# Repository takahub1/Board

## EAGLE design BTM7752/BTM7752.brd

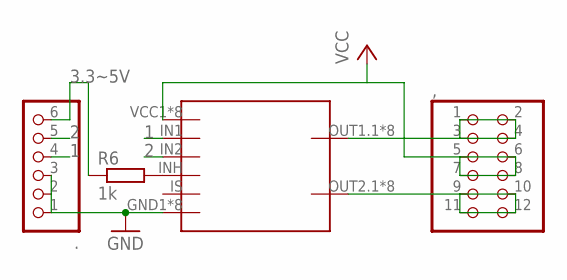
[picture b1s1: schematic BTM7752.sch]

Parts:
,: PINHD-2X6; 2X06
.: PINHD-1X6; 1X06
R6: 1k; R0603
U$1: BTM7752

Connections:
1: ..4, U$1.IN1
2: ..5, U$1.IN2
3.3~5V: ..6, R6.1
GND: ..1, ..2, ..3, U$1.GND1 (GND), U$1.GND2 (GND), U$1.GND3 (GND), U$1.GND4 (GND), U$1.GND5 (GND), U$1.GND6 (GND), U$1.GND7 (GND), U$1.GND8 (GND)
unnamed: ,.9, ,.10, ,.11, ,.12, U$1.OUT2.1 (OUT2), U$1.OUT2.2 (OUT2), U$1.OUT2.3 (OUT2), U$1.OUT2.4 (OUT2), U$1.OUT2.5 (OUT2), U$1.OUT2.6 (OUT2), U$1.OUT2.7 (OUT2), U$1.OUT2.8 (OUT2)
unnamed: ,.1, ,.2, ,.3, ,.4, U$1.OUT1.1 (OUT1), U$1.OUT1.2 (OUT1), U$1.OUT1.3 (OUT1), U$1.OUT1.4 (OUT1), U$1.OUT1.5 (OUT1), U$1.OUT1.6 (OUT1), U$1.OUT1.7 (OUT1), U$1.OUT1.8 (OUT1)
unnamed: R6.2, U$1.INH
VCC: ,.5, ,.6, ,.7, ,.8, U$1.VCC1 (VCC), U$1.VCC2 (VCC), U$1.VCC3 (VCC), U$1.VCC4 (VCC), U$1.VCC5 (VCC), U$1.VCC6 (VCC), U$1.VCC7 (VCC), U$1.VCC8 (VCC)

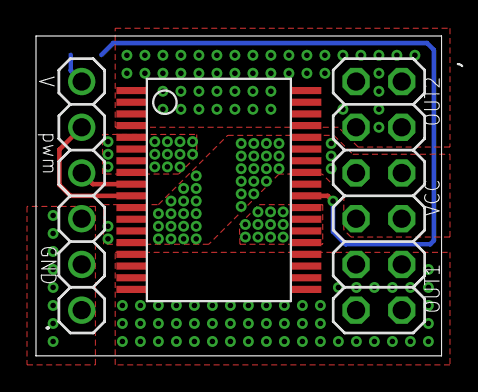
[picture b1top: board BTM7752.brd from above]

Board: 2 copper layers, 22.5 x 17.8 mm, 4 parts (1 on the bottom side), 8 nets.

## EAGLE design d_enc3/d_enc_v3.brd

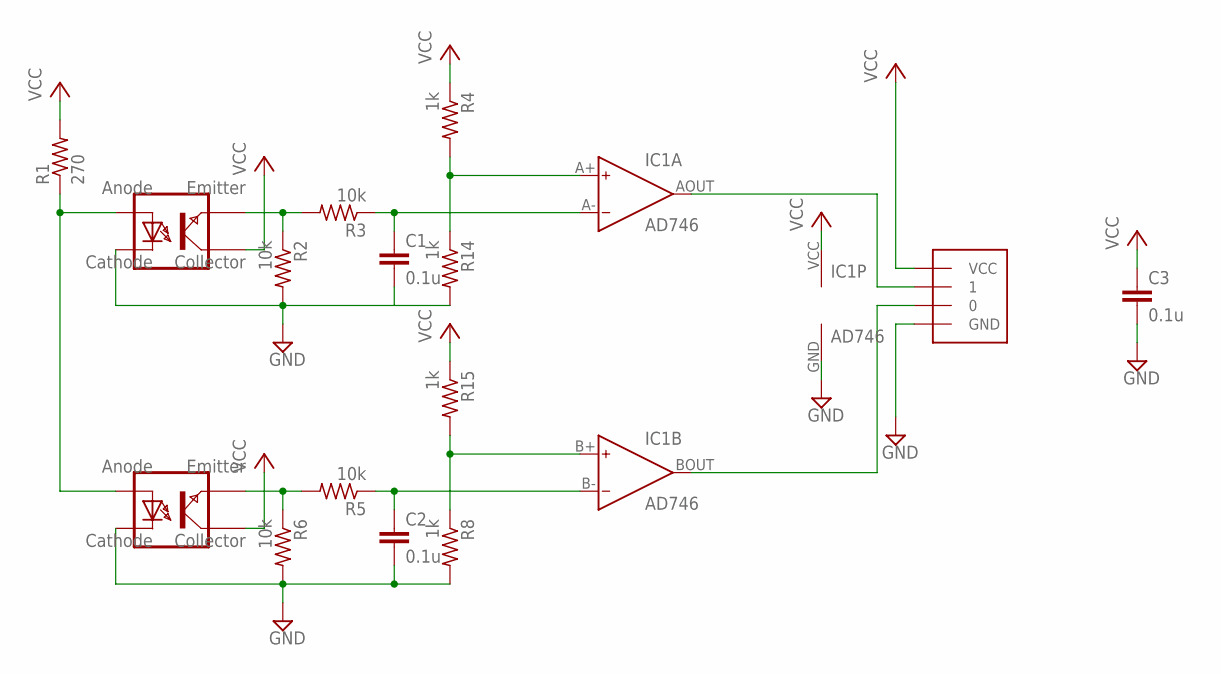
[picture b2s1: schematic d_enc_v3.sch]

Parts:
C1, C2, C3: 0.1u; C0603
IC1: AD746; NJM2903E
R1: 270; R0603
R2, R3, R5, R6: 10k; R0603
R4, R8, R14, R15: 1k; R0603
U$1, U$4: TPR-105F
U$2: ENC_CON

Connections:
GND: C1.2, C2.2, C3.2, IC1.GND (V-), R2.2, R6.2, R8.2, R14.2, U$1.CATHODE, U$2.GND, U$4.CATHODE
unnamed: C1.1, IC1.A- (IN-), R3.1
unnamed: R1.1, U$1.ANODE, U$4.ANODE
unnamed: R2.1, R3.2, U$4.EMITTER
unnamed: R5.2, R6.1, U$1.EMITTER
unnamed: C2.1, IC1.B- (IN-), R5.1
unnamed: IC1.AOUT (OUT), U$2.1
unnamed: IC1.BOUT (OUT), U$2.0
unnamed: IC1.B+ (IN+), R8.1, R15.2
unnamed: IC1.A+ (IN+), R4.2, R14.1
VCC: C3.1, IC1.VCC (V+), R1.2, R4.1, R15.1, U$1.COLLECTOR, U$2.VCC, U$4.COLLECTOR

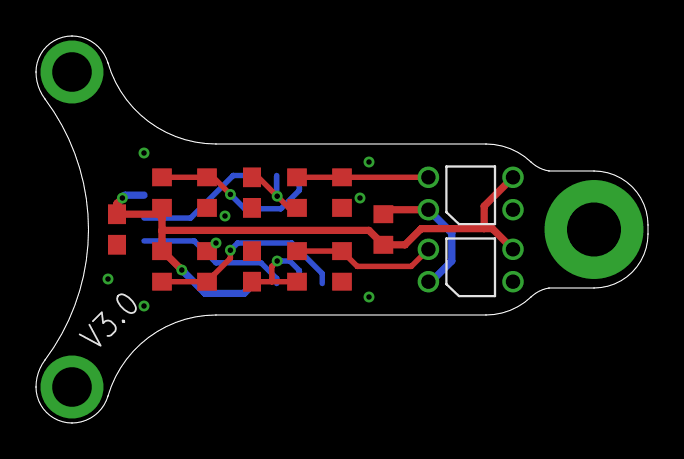
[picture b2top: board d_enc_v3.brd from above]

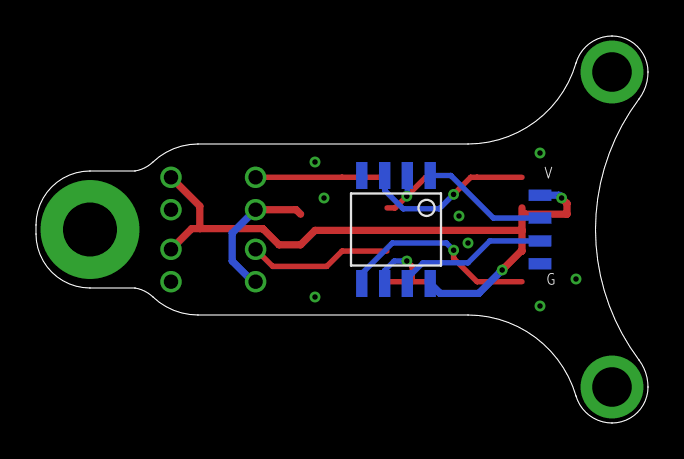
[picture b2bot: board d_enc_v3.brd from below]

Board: 2 copper layers, 34.0 x 21.5 mm, 16 parts (2 on the bottom side), 11 nets.

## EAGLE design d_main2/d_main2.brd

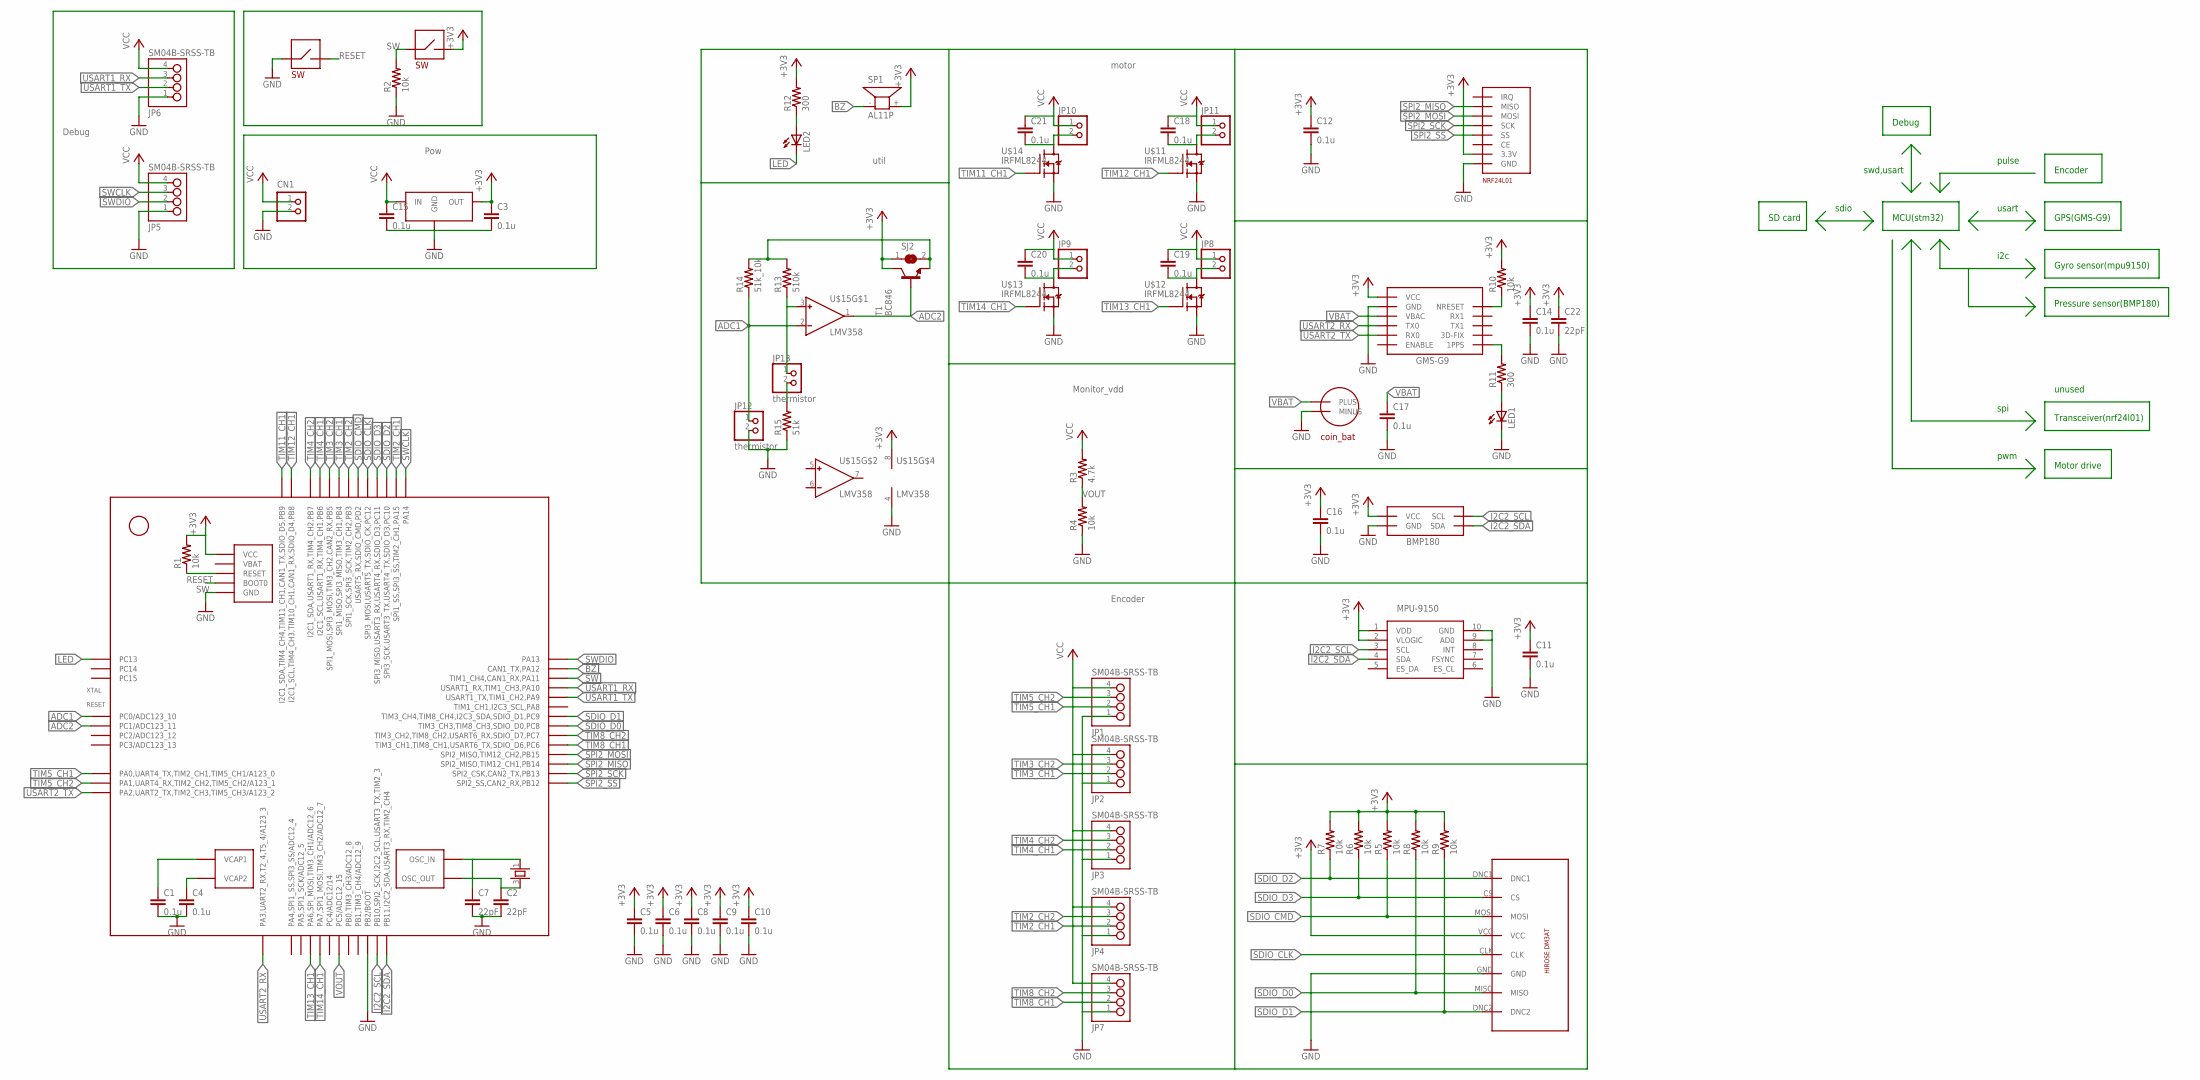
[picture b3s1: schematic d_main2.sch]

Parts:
C1, C3, C4, C5, C6, C8, C9, C10, C11, C12, C14, C15, C16, C17, C18, C19, C20, C21: 0.1u; C0603K
C2, C7, C22: 22pF; C0603K
CN1: S2B-XASK-1
JP1, JP2, JP3, JP4, JP5, JP6, JP7: SM04B-SRSS-TB
JP8, JP9, JP10, JP11: PINHD-1X2; 1X02
JP12, JP13: thermistor; 1X02
LED1, LED2: LEDCHIP-LED0603; CHIP-LED0603
R1, R2, R4, R5, R6, R7, R8, R9, R10: 10k; R0603
R3: 4.7k; R0603
R11, R12: 300; R0603
R13: 510k; R0603
R14: 51k_10k; R0603
R15: 51k; R0603
SJ2: SJ
SP1: AL11P
STM32F405RGT6: STM32F405_T; LQFP64
T1: BC846; SOT23
U$1: GMS-G9
U$2: BMP180
U$3: NRF24L01
U$4: 1056TR
U$5: DM3AT
U$6, U$7: SWTVBP06-B043CB-B; SW
U$8: AP7361-33E; SOT223
U$9: 25MHz; ASF
U$10: MPU-9150
U$11, U$12, U$13, U$14: IRFML8244; SOT23
U$15: LMV358; SO8

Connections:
+3V3: C3.1, C5.1, C6.1, C8.1, C9.1, C10.1, C11.1, C12.1, C14.1, C16.1, C22.1, R1.2, R5.2, R6.2, R7.2, R8.2, R9.2, R10.2, R12.2, SJ2.1, SP1.+ (2), STM32F405RGT6.13 (VCC), STM32F405RGT6.19 (VCC), STM32F405RGT6.32 (VCC), STM32F405RGT6.48 (VCC), STM32F405RGT6.64 (VCC), T1.3 (C), U$1.VCC, U$2.VDD (VCC), U$2.VDDIO (VCC), U$3.3.3V, U$5.VCC, U$7.P$2, U$8.OUT, U$10.1 (VDD), U$10.2 (VLOGIC), U$15.8 (V+)
ADC1: JP12.1, R14.1, STM32F405RGT6.8 (PC0/ADC123_10), U$15.2 (IN-)
ADC2: STM32F405RGT6.9 (PC1/ADC123_11), T1.1 (B), U$15.1 (OUT)
BZ: SP1.- (1), STM32F405RGT6.45 (CAN1_TX,PA12)
GND: C1.2, C2.2, C3.2, C4.2, C5.2, C6.2, C7.2, C8.2, C9.2, C10.2, C11.2, C12.2, C14.2, C15.2, C16.2, C17.2, C22.2, CN1.2, JP1.1, JP2.1, JP3.1, JP4.1, JP5.1, JP6.1, JP7.1, JP12.2, LED1.C, R2.1, R4.1, R15.1, STM32F405RGT6.12 (GND), STM32F405RGT6.18 (GND), STM32F405RGT6.28 (PB2/BOOT), STM32F405RGT6.63 (GND), U$1.GND, U$1.GND1 (GND), U$2.GND, U$3.GND, U$4.MINUS, U$5.GND, U$6.P$1, U$8.GND1 (GND), U$8.GND2 (GND), U$10.9 (AD0), U$10.10 (GND), U$11.2 (S), U$12.2 (S), U$13.2 (S), U$14.2 (S), U$15.4 (V-)
I2C2_SCL: STM32F405RGT6.29 (PB10,SPI2_SCK,I2C2_SCL,USART3_TX,TIM2_3), U$2.SCL, U$10.3 (SCL)
I2C2_SDA: STM32F405RGT6.30 (PB11,I2C2_SDA,USART3_RX,TIM2_CH4), U$2.SDA, U$10.4 (SDA)
LED: LED2.C, STM32F405RGT6.2 (PC13)
unnamed: C4.1, STM32F405RGT6.47 (VCAP2)
unnamed: C1.1, STM32F405RGT6.31 (VCAP1)
unnamed: C7.1, STM32F405RGT6.5 (OSC_IN), U$9.1
unnamed: C2.1, STM32F405RGT6.6 (OSC_OUT), U$9.3
unnamed: R10.1, U$1.NRESET
unnamed: R11.2, U$1.1PPS
unnamed: LED1.A, R11.1
unnamed: LED2.A, R12.1
unnamed: C18.2, JP11.2, U$11.3 (D)
unnamed: C19.2, JP8.2, U$12.3 (D)
unnamed: C20.2, JP9.2, U$13.3 (D)
unnamed: C21.2, JP10.2, U$14.3 (D)
unnamed: JP13.1, R13.1, U$15.3 (IN+)
unnamed: R13.2, R14.2, SJ2.2, T1.2 (E)
unnamed: JP13.2, R15.2
RESET: R1.1, STM32F405RGT6.7 (RESET), U$6.P$2
SDIO_CLK: STM32F405RGT6.53 (SPI3_MOSI,USART5_TX,SDIO_CK,PC12), U$5.CLK
SDIO_CMD: R5.1, STM32F405RGT6.54 (USART5_RX,SDIO_CMD,PD2), U$5.MOSI
SDIO_D0: R8.1, STM32F405RGT6.39 (TIM3_CH3,TIM8_CH3,SDIO_D0,PC8), U$5.MISO
SDIO_D1: R9.1, STM32F405RGT6.40 (TIM3_CH4,TIM8_CH4,I2C3_SDA,SDIO_D1,PC9), U$5.DNC2
SDIO_D2: R7.1, STM32F405RGT6.51 (SPI3_SCK,USART3_TX,USART4_TX,SDIO_D3,PC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), U$5.DNC1
SDIO_D3: R6.1, STM32F405RGT6.52 (SPI3_MISO,USART3_RX,USART4_RX,SDIO_D3,P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), U$5.CS
SPI2_MISO: STM32F405RGT6.35 (SPI2_MISO,TIM12_CH1,PB14), U$3.MISO
SPI2_MOSI: STM32F405RGT6.36 (SPI2_MISO,TIM12_CH2,PB15), U$3.MOSI
SPI2_SCK: STM32F405RGT6.34 (SPI2_CSK,CAN2_TX,PB13), U$3.SCK
SPI2_SS: STM32F405RGT6.33 (SPI2_SS,CAN2_RX,PB12), U$3.SS
SW: R2.2, STM32F405RGT6.44 (TIM1_CH4,CAN1_RX,PA11), STM32F405RGT6.60 (BOOT0), U$7.P$1
SWCLK: JP5.3, STM32F405RGT6.49 (PA14)
SWDIO: JP5.2, STM32F405RGT6.46 (PA13)
TIM2_CH1: JP4.2, STM32F405RGT6.50 (SPI1_SS,SPI3_SS,TIM2_CH1,PA15)
TIM2_CH2: JP4.3, STM32F405RGT6.55 (SPI1_SCK,SPI3_SCK,TIM2_CH2,PB3)
TIM3_CH1: JP2.2, STM32F405RGT6.56 (SPI1_MISO,SPI3_MISO,TIM3_CH1,PB4)
TIM3_CH2: JP2.3, STM32F405RGT6.57 (SPI1_MOSI,SPI3_MOSI,TIM3_CH2,CAN2_RX,PB5)
TIM4_CH1: JP3.2, STM32F405RGT6.58 (I2C1_SCL,USART1_RX,TIM4_CH1,PB6)
TIM4_CH2: JP3.3, STM32F405RGT6.59 (I2C1_SDA,USART1_RX,TIM4_CH2,PB7)
TIM5_CH1: JP1.2, STM32F405RGT6.14 (PA0,UART4_TX,TIM2_CH1,TIM5_CH1/A123_0)
TIM5_CH2: JP1.3, STM32F405RGT6.15 (PA1,UART4_RX,TIM2_CH2,TIM5_CH2/A123_1)
TIM8_CH1: JP7.2, STM32F405RGT6.37 (TIM3_CH1,TIM8_CH1,USART6_TX,SDIO_D6,PC6)
TIM8_CH2: JP7.3, STM32F405RGT6.38 (TIM3_CH2,TIM8_CH2,USART6_RX,SDIO_D7,PC7)
TIM11_CH1: STM32F405RGT6.62 (I2C1_SDA,TIM4_CH4,TIM11_CH1,CAN1_TX,SDI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), U$14.1 (G)
TIM12_CH1: STM32F405RGT6.61 (I2C1_SCL,TIM4_CH3,TIM10_CH1,CAN1_RX,SDI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), U$11.1 (G)
TIM13_CH1: STM32F405RGT6.22 (PA6,SPI_MOSI,TIM3_CH1/ADC12_6), U$12.1 (G)
TIM14_CH1: STM32F405RGT6.23 (PA7,SPI1_MOSI,TIM3_CH2/ADC12_7), U$13.1 (G)
USART1_RX: JP6.3, STM32F405RGT6.43 (USART1_RX,TIM1_CH3,PA10)
USART1_TX: JP6.2, STM32F405RGT6.42 (USART1_TX,TIM1_CH2,PA9)
USART2_RX: STM32F405RGT6.17 (PA3,UART2_RX,T2_4,T5_4/A123_3), U$1.TX0
USART2_TX: STM32F405RGT6.16 (PA2,UART2_TX,TIM2_CH3,TIM5_CH3/A123_2), U$1.RX0
VBAT: C17.1, U$1.VBAC, U$4.PLUS
VCC: C15.1, C18.1, C19.1, C20.1, C21.1, CN1.1, JP1.4, JP2.4, JP3.4, JP4.4, JP5.4, JP6.4, JP7.4, JP8.1, JP9.1, JP10.1, JP11.1, R3.2, U$8.IN
VOUT: R3.1, R4.2, STM32F405RGT6.25 (PC5/ADC12_15)

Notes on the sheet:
Debug
Pow
Encoder
Monitor_vdd
motor
util
MCU(stm32)
Gyro sensor(mpu9150)
Pressure sensor(BMP180)
GPS(GMS-G9)
SD card
i2c
usart
swd,usart
pulse
sdio
unused
Transceiver(nrf24l01)
Motor drive
spi
pwm

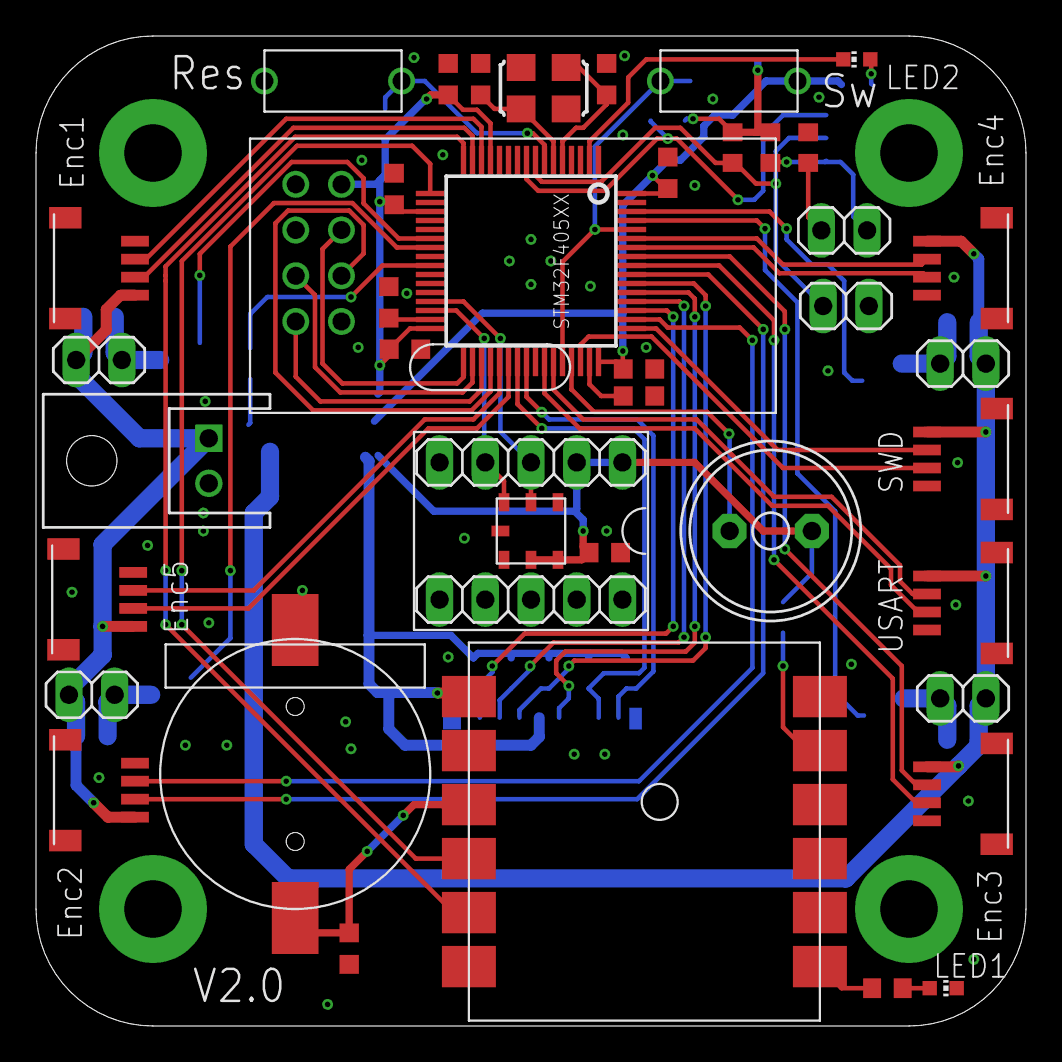
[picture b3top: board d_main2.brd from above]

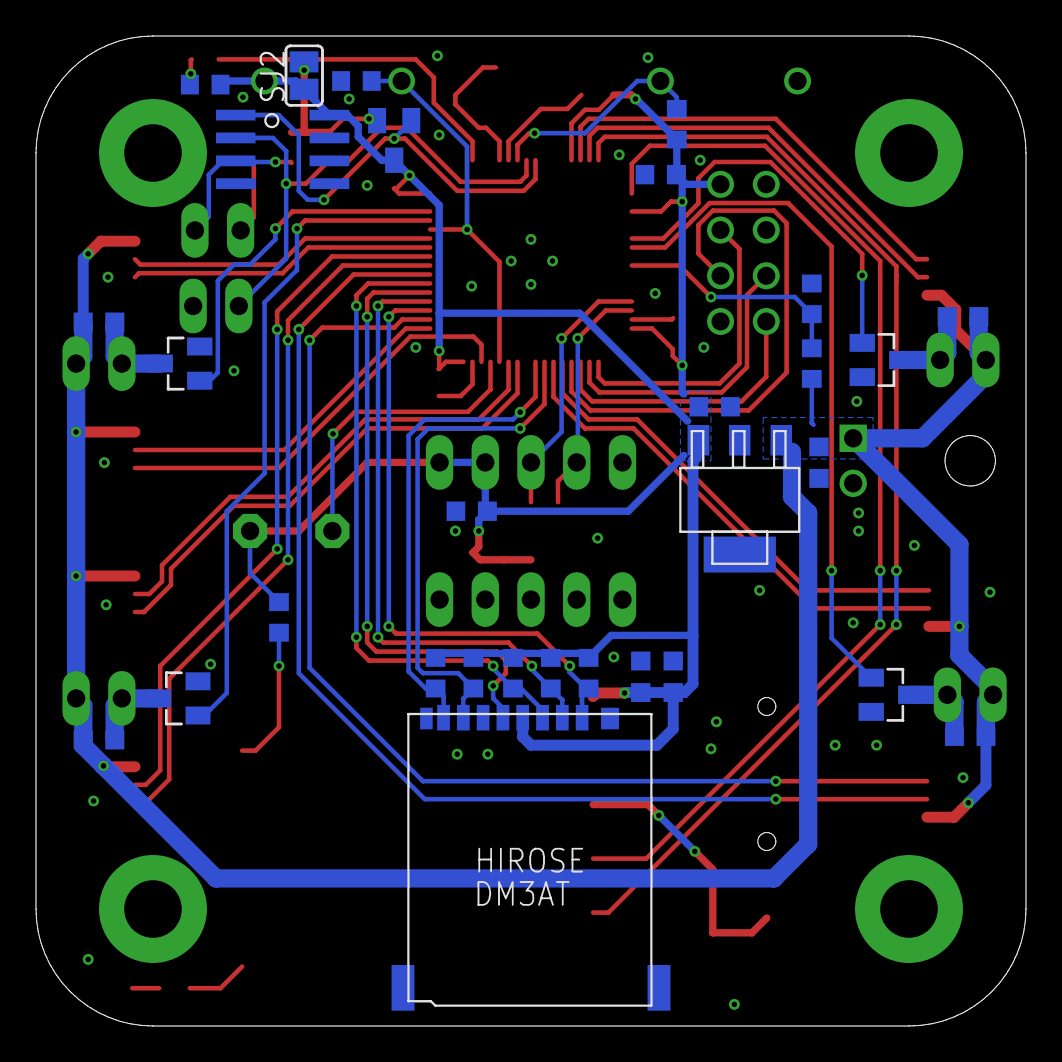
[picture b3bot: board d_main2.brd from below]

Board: 2 copper layers, 55.0 x 55.0 mm, 71 parts (30 on the bottom side), 58 nets.

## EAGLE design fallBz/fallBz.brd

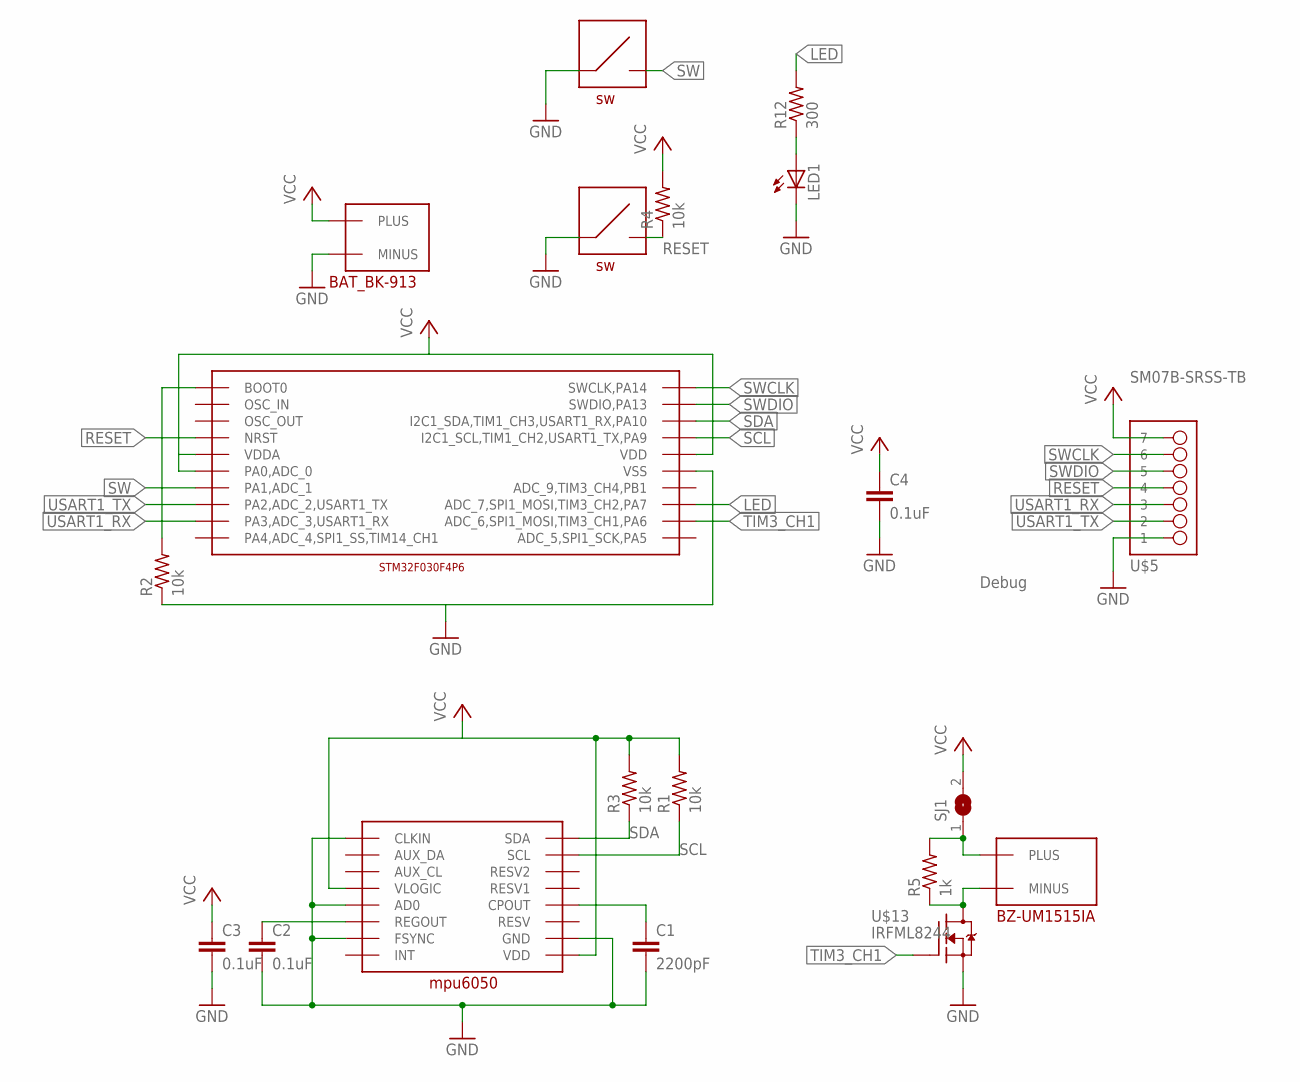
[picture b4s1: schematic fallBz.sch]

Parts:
C1: 2200pF; C0603K
C2, C3, C4: 0.1uF; C0603K
GH: BAT_BK-913
LED1: LEDCHIP-LED0603; CHIP-LED0603
R1, R2, R3, R4: 10k; R0603
R5: 1k; R0603
R12: 300; R0603
SJ1: SJ
U$1: STM-TSSOP20
U$2: BZ-UM1515IA
U$3: MPU6050
U$4, U$7: KMT071-NGJ-LHS
U$5: SM07B-SRSS-TB
U$13: IRFML8244; SOT23

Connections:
GND: C1.2, C2.2, C3.2, C4.2, GH.MINUS, LED1.C, R2.1, U$1.P$15 (VSS), U$3.AD0, U$3.CLKIN, U$3.FSYNC, U$3.GND, U$4.SW00, U$4.SW0, U$5.P$1 (1), U$7.SW00, U$7.SW0, U$13.2 (S)
LED: R12.2, U$1.P$13 (ADC_7,SPI1_MOSI,TIM3_CH2,PA7)
unnamed: C2.1, U$3.REGOUT
unnamed: R5.1, U$2.MINUS, U$13.3 (D)
unnamed: R5.2, SJ1.1, U$2.PLUS
unnamed: C1.1, U$3.CPOUT
unnamed: R2.2, U$1.P$1 (BOOT0)
unnamed: LED1.A, R12.1
RESET: R4.1, U$1.P$4 (NRST), U$5.P$4 (4), U$7.SW1, U$7.SW11
SCL: R1.1, U$1.P$17 (I2C1_SCL,TIM1_CH2,USART1_TX,PA9), U$3.SCL
SDA: R3.1, U$1.P$18 (I2C1_SDA,TIM1_CH3,USART1_RX,PA10), U$3.SDA
SW: U$1.P$7 (PA1,ADC_1), U$4.SW1, U$4.SW11
SWCLK: U$1.P$20 (SWCLK,PA14), U$5.P$6 (6)
SWDIO: U$1.P$19 (SWDIO,PA13), U$5.P$5 (5)
TIM3_CH1: U$1.P$12 (ADC_6,SPI1_MOSI,TIM3_CH1,PA6), U$13.1 (G)
USART1_RX: U$1.P$9 (PA3,ADC_3,USART1_RX), U$5.P$3 (3)
USART1_TX: U$1.P$8 (PA2,ADC_2,USART1_TX), U$5.P$2 (2)
VCC: C3.1, C4.1, GH.PLUS0 (PLUS), GH.PLUS1 (PLUS), R1.2, R3.2, R4.2, SJ1.2, U$1.P$5 (VDDA), U$1.P$6 (PA0,ADC_0), U$1.P$16 (VDD), U$3.VDD, U$3.VLOGIC, U$5.P$7 (7)

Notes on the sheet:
Debug

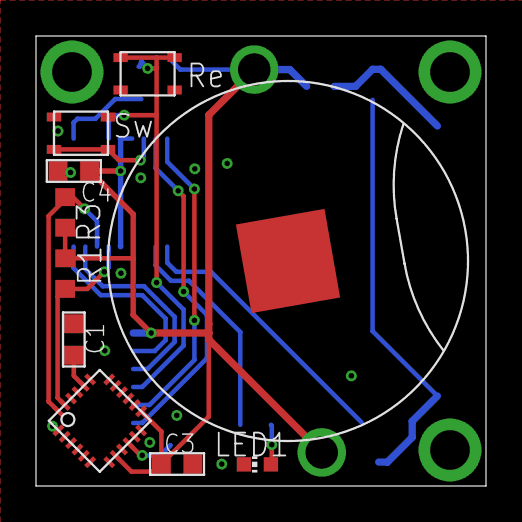
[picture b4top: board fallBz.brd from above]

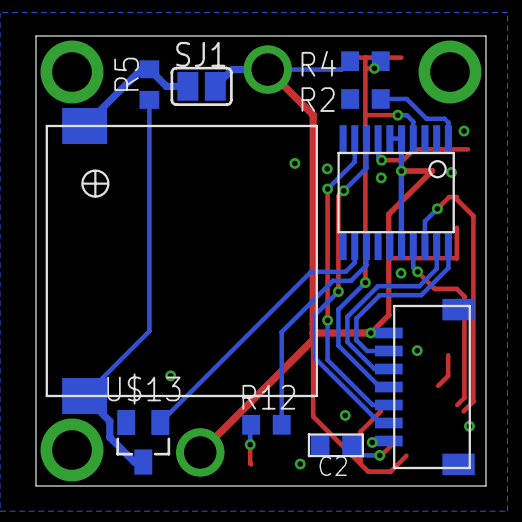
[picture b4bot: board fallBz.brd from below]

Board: 2 copper layers, 25.0 x 25.0 mm, 20 parts (10 on the bottom side), 18 nets.

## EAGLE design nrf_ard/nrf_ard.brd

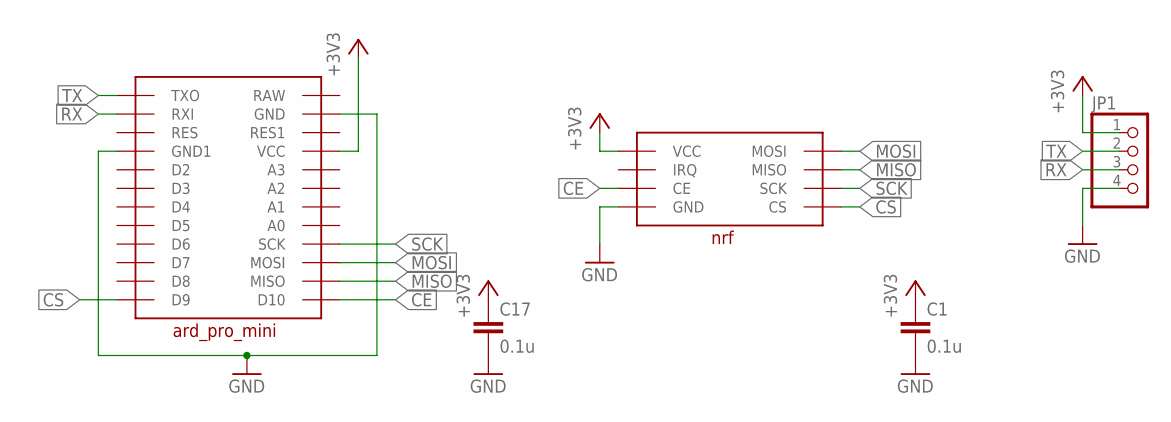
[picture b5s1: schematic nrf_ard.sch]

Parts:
C1, C17: 0.1u; C0603K
JP1: PINHD-1X4; 1X04
U$1: ARD_PRO_MINI
U$2: NRF

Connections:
+3V3: C1.1, C17.1, JP1.1, U$1.VCC, U$2.VCC
CE: U$1.D10, U$2.CE
CS: U$1.D9, U$2.CS
GND: C1.2, C17.2, JP1.4, U$1.GND1 (GND), U$1.GND2 (GND1), U$2.GND
MISO: U$1.MISO, U$2.MISO
MOSI: U$1.MOSI, U$2.MOSI
RX: JP1.3, U$1.RXI
SCK: U$1.SCK, U$2.SCK
TX: JP1.2, U$1.TXO

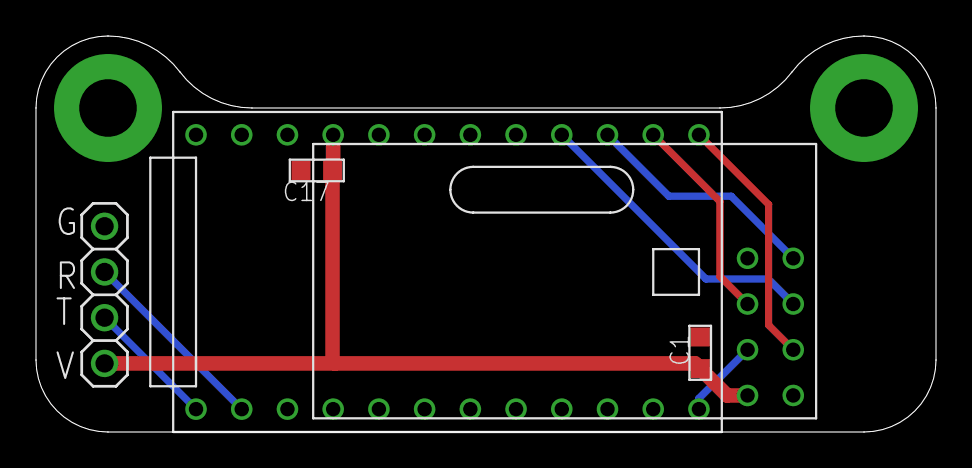
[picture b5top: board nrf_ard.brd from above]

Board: 2 copper layers, 50.0 x 22.0 mm, 5 parts (0 on the bottom side), 9 nets.
